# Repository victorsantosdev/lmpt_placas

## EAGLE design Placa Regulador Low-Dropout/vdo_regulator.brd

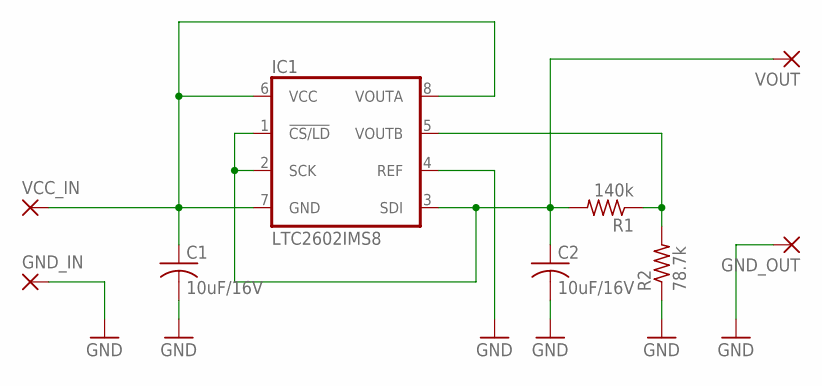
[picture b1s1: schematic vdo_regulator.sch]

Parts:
C1, C2: 10uF/16V; C025-025X050
GND_IN: 2,54/0,9
GND_OUT: 2,54/0,9
IC1: LTC2602IMS8; MSOP8
R1: 140k; 0309/10
R2: 78.7k; 0309/10
VCC_IN: 2,54/0,9
VOUT: 2,54/0,9

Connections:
GND: C1.2, C2.2, GND_IN.1, GND_OUT.1, IC1.4 (REF), R2.1
unnamed: C1.1, IC1.6 (VCC), IC1.7 (GND), IC1.8 (VOUTA), VCC_IN.1
unnamed: C2.1, IC1.1 (!CS/LD), IC1.2 (SCK), IC1.3 (SDI), R1.2, VOUT.1
unnamed: IC1.5 (VOUTB), R1.1, R2.2

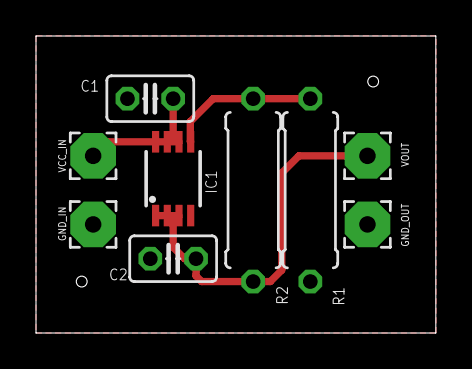
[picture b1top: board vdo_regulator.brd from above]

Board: 2 copper layers, 22.2 x 16.5 mm, 9 parts (0 on the bottom side), 4 nets.

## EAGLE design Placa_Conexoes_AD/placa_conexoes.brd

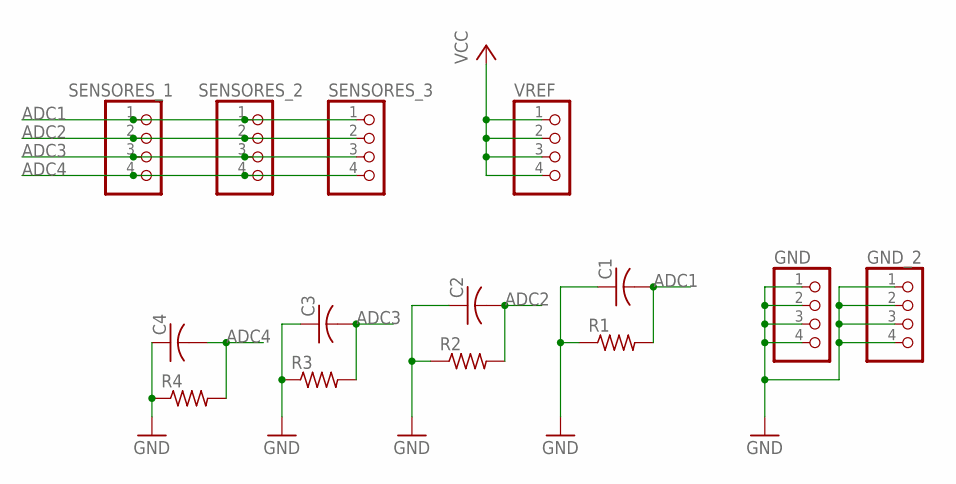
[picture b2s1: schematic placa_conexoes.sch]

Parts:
C1, C2, C3, C4: C-US025-025X050; C025-025X050
GND: PINHD-1X4; 1X04
GND_2: PINHD-1X4; 1X04
R1, R2, R3, R4: R-US_0207/9; 0207/9
SENSORES_1, SENSORES_2, SENSORES_3: PINHD-1X4; 1X04
VREF: PINHD-1X4; 1X04

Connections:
ADC1: C1.2, R1.2, SENSORES_1.1, SENSORES_2.1, SENSORES_3.1
ADC2: C2.2, R2.2, SENSORES_1.2, SENSORES_2.2, SENSORES_3.2
ADC3: C3.2, R3.2, SENSORES_1.3, SENSORES_2.3, SENSORES_3.3
ADC4: C4.2, R4.2, SENSORES_1.4, SENSORES_2.4, SENSORES_3.4
GND: C1.1, C2.1, C3.1, C4.1, GND.1, GND.2, GND.3, GND.4, GND_2.1, GND_2.2, GND_2.3, GND_2.4, R1.1, R2.1, R3.1, R4.1
VCC: VREF.1, VREF.2, VREF.3, VREF.4

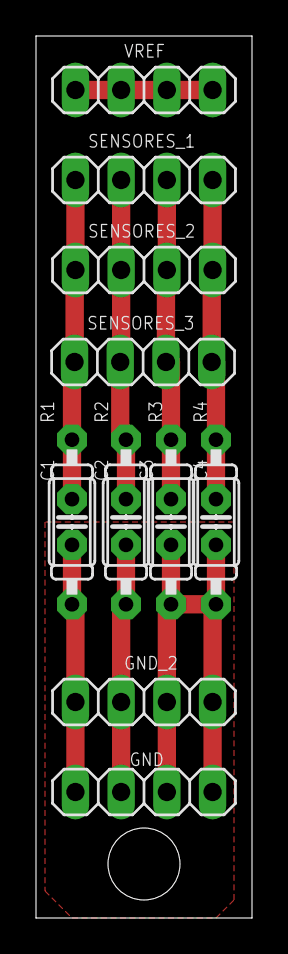
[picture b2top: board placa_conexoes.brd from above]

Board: 2 copper layers, 12.0 x 49.0 mm, 14 parts (0 on the bottom side), 6 nets.

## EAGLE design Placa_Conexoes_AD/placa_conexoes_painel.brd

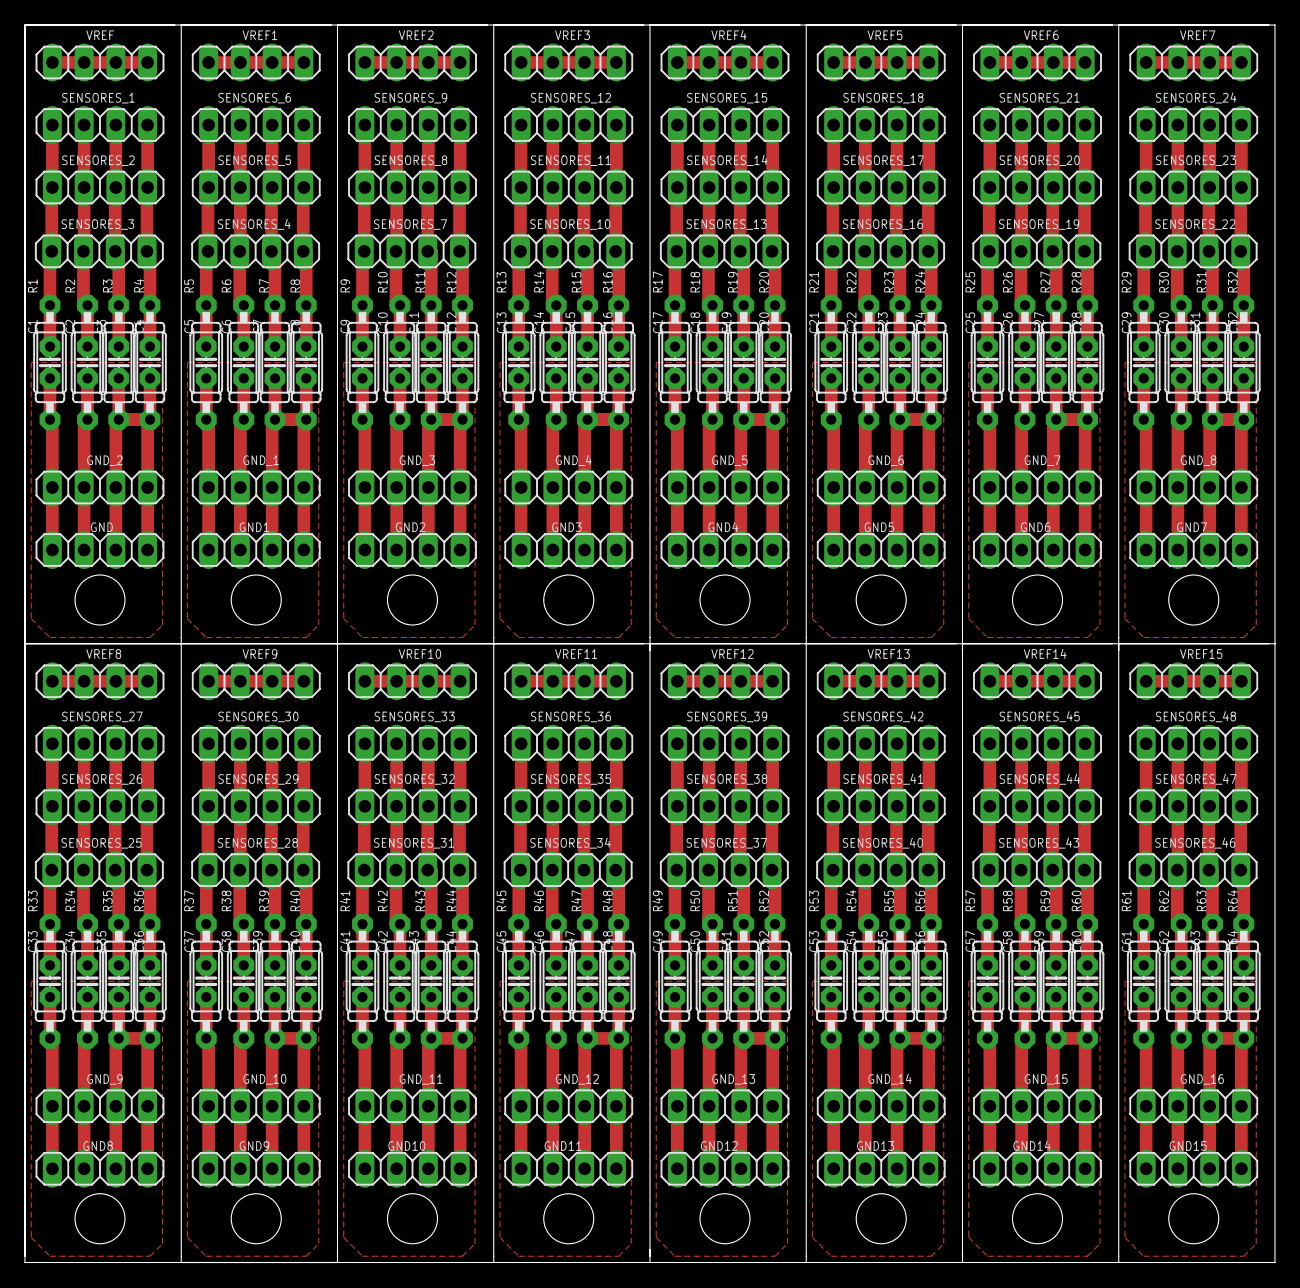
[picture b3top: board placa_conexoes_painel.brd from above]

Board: 2 copper layers, 100.0 x 99.0 mm, 224 parts (0 on the bottom side), 96 nets.

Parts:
C1, C2, C3, C4, C5, C6, C7, C8, C9, C10, C11, C12, C13, C14, C15, C16, C17, C18, C19, C20, C21, C22, C23, C24, C25, C26, C27, C28, C29, C30, C31, C32, C33, C34, C35, C36, C37, C38, C39, C40, C41, C42, C43, C44, C45, C46, C47, C48, C49, C50, C51, C52, C53, C54, C55, C56, C57, C58, C59, C60, C61, C62, C63, C64: C025-025X050
GND, GND1, GND2, GND3, GND4, GND5, GND6, GND7, GND8, GND9, GND10, GND11, GND12, GND13, GND14, GND15: 1X04
GND_1, GND_2, GND_3, GND_4, GND_5, GND_6, GND_7, GND_8, GND_9, GND_10, GND_11, GND_12, GND_13, GND_14, GND_15, GND_16: 1X04
R1, R2, R3, R4, R5, R6, R7, R8, R9, R10, R11, R12, R13, R14, R15, R16, R17, R18, R19, R20, R21, R22, R23, R24, R25, R26, R27, R28, R29, R30, R31, R32, R33, R34, R35, R36, R37, R38, R39, R40, R41, R42, R43, R44, R45, R46, R47, R48, R49, R50, R51, R52, R53, R54, R55, R56, R57, R58, R59, R60, R61, R62, R63, R64: 0207/9
SENSORES_1, SENSORES_2, SENSORES_3, SENSORES_4, SENSORES_5, SENSORES_6, SENSORES_7, SENSORES_8, SENSORES_9, SENSORES_10, SENSORES_11, SENSORES_12, SENSORES_13, SENSORES_14, SENSORES_15, SENSORES_16, SENSORES_17, SENSORES_18, SENSORES_19, SENSORES_20, SENSORES_21, SENSORES_22, SENSORES_23, SENSORES_24, SENSORES_25, SENSORES_26, SENSORES_27, SENSORES_28, SENSORES_29, SENSORES_30, SENSORES_31, SENSORES_32, SENSORES_33, SENSORES_34, SENSORES_35, SENSORES_36, SENSORES_37, SENSORES_38, SENSORES_39, SENSORES_40, SENSORES_41, SENSORES_42, SENSORES_43, SENSORES_44, SENSORES_45, SENSORES_46, SENSORES_47, SENSORES_48: 1X04
VREF, VREF1, VREF2, VREF3, VREF4, VREF5, VREF6, VREF7, VREF8, VREF9, VREF10, VREF11, VREF12, VREF13, VREF14, VREF15: 1X04

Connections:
ADC1: C1.2, R1.2, SENSORES_1.1, SENSORES_2.1, SENSORES_3.1
ADC2: C2.2, R2.2, SENSORES_1.2, SENSORES_2.2, SENSORES_3.2
ADC3: C3.2, R3.2, SENSORES_1.3, SENSORES_2.3, SENSORES_3.3
ADC4: C4.2, R4.2, SENSORES_1.4, SENSORES_2.4, SENSORES_3.4
ADC5: C8.2, R8.2, SENSORES_4.4, SENSORES_5.4, SENSORES_6.4
ADC6: C7.2, R7.2, SENSORES_4.3, SENSORES_5.3, SENSORES_6.3
ADC7: C6.2, R6.2, SENSORES_4.2, SENSORES_5.2, SENSORES_6.2
ADC8: C5.2, R5.2, SENSORES_4.1, SENSORES_5.1, SENSORES_6.1
ADC9: C12.2, R12.2, SENSORES_7.4, SENSORES_8.4, SENSORES_9.4
ADC10: C11.2, R11.2, SENSORES_7.3, SENSORES_8.3, SENSORES_9.3
ADC11: C10.2, R10.2, SENSORES_7.2, SENSORES_8.2, SENSORES_9.2
ADC12: C9.2, R9.2, SENSORES_7.1, SENSORES_8.1, SENSORES_9.1
ADC13: C16.2, R16.2, SENSORES_10.4, SENSORES_11.4, SENSORES_12.4
ADC14: C15.2, R15.2, SENSORES_10.3, SENSORES_11.3, SENSORES_12.3
ADC15: C14.2, R14.2, SENSORES_10.2, SENSORES_11.2, SENSORES_12.2
ADC16: C13.2, R13.2, SENSORES_10.1, SENSORES_11.1, SENSORES_12.1
ADC17: C20.2, R20.2, SENSORES_13.4, SENSORES_14.4, SENSORES_15.4
ADC18: C19.2, R19.2, SENSORES_13.3, SENSORES_14.3, SENSORES_15.3
ADC19: C18.2, R18.2, SENSORES_13.2, SENSORES_14.2, SENSORES_15.2
ADC20: C17.2, R17.2, SENSORES_13.1, SENSORES_14.1, SENSORES_15.1
ADC21: C24.2, R24.2, SENSORES_16.4, SENSORES_17.4, SENSORES_18.4
ADC22: C23.2, R23.2, SENSORES_16.3, SENSORES_17.3, SENSORES_18.3
ADC23: C22.2, R22.2, SENSORES_16.2, SENSORES_17.2, SENSORES_18.2
ADC24: C21.2, R21.2, SENSORES_16.1, SENSORES_17.1, SENSORES_18.1
ADC25: C28.2, R28.2, SENSORES_19.4, SENSORES_20.4, SENSORES_21.4
ADC26: C27.2, R27.2, SENSORES_19.3, SENSORES_20.3, SENSORES_21.3
ADC27: C26.2, R26.2, SENSORES_19.2, SENSORES_20.2, SENSORES_21.2
ADC28: C25.2, R25.2, SENSORES_19.1, SENSORES_20.1, SENSORES_21.1
ADC29: C32.2, R32.2, SENSORES_22.4, SENSORES_23.4, SENSORES_24.4
ADC30: C31.2, R31.2, SENSORES_22.3, SENSORES_23.3, SENSORES_24.3
ADC31: C30.2, R30.2, SENSORES_22.2, SENSORES_23.2, SENSORES_24.2
ADC32: C29.2, R29.2, SENSORES_22.1, SENSORES_23.1, SENSORES_24.1
ADC33: C36.2, R36.2, SENSORES_25.4, SENSORES_26.4, SENSORES_27.4
ADC34: C35.2, R35.2, SENSORES_25.3, SENSORES_26.3, SENSORES_27.3
ADC35: C34.2, R34.2, SENSORES_25.2, SENSORES_26.2, SENSORES_27.2
ADC36: C33.2, R33.2, SENSORES_25.1, SENSORES_26.1, SENSORES_27.1
ADC37: C40.2, R40.2, SENSORES_28.4, SENSORES_29.4, SENSORES_30.4
ADC38: C39.2, R39.2, SENSORES_28.3, SENSORES_29.3, SENSORES_30.3
ADC39: C38.2, R38.2, SENSORES_28.2, SENSORES_29.2, SENSORES_30.2
ADC40: C37.2, R37.2, SENSORES_28.1, SENSORES_29.1, SENSORES_30.1
ADC41: C44.2, R44.2, SENSORES_31.4, SENSORES_32.4, SENSORES_33.4
ADC42: C43.2, R43.2, SENSORES_31.3, SENSORES_32.3, SENSORES_33.3
ADC43: C42.2, R42.2, SENSORES_31.2, SENSORES_32.2, SENSORES_33.2
ADC44: C41.2, R41.2, SENSORES_31.1, SENSORES_32.1, SENSORES_33.1
ADC45: C48.2, R48.2, SENSORES_34.4, SENSORES_35.4, SENSORES_36.4
ADC46: C47.2, R47.2, SENSORES_34.3, SENSORES_35.3, SENSORES_36.3
ADC47: C46.2, R46.2, SENSORES_34.2, SENSORES_35.2, SENSORES_36.2
ADC48: C45.2, R45.2, SENSORES_34.1, SENSORES_35.1, SENSORES_36.1
ADC49: C52.2, R52.2, SENSORES_37.4, SENSORES_38.4, SENSORES_39.4
ADC50: C51.2, R51.2, SENSORES_37.3, SENSORES_38.3, SENSORES_39.3
ADC51: C50.2, R50.2, SENSORES_37.2, SENSORES_38.2, SENSORES_39.2
ADC52: C49.2, R49.2, SENSORES_37.1, SENSORES_38.1, SENSORES_39.1
ADC53: C56.2, R56.2, SENSORES_40.4, SENSORES_41.4, SENSORES_42.4
ADC54: C55.2, R55.2, SENSORES_40.3, SENSORES_41.3, SENSORES_42.3
ADC55: C54.2, R54.2, SENSORES_40.2, SENSORES_41.2, SENSORES_42.2
ADC56: C53.2, R53.2, SENSORES_40.1, SENSORES_41.1, SENSORES_42.1
ADC57: C60.2, R60.2, SENSORES_43.4, SENSORES_44.4, SENSORES_45.4
ADC58: C59.2, R59.2, SENSORES_43.3, SENSORES_44.3, SENSORES_45.3
ADC59: C58.2, R58.2, SENSORES_43.2, SENSORES_44.2, SENSORES_45.2
ADC60: C57.2, R57.2, SENSORES_43.1, SENSORES_44.1, SENSORES_45.1
ADC61: C64.2, R64.2, SENSORES_46.4, SENSORES_47.4, SENSORES_48.4
ADC62: C63.2, R63.2, SENSORES_46.3, SENSORES_47.3, SENSORES_48.3
ADC63: C62.2, R62.2, SENSORES_46.2, SENSORES_47.2, SENSORES_48.2
ADC64: C61.2, R61.2, SENSORES_46.1, SENSORES_47.1, SENSORES_48.1
GND: C1.1, C2.1, C3.1, C4.1, GND.1, GND.2, GND.3, GND.4, GND_2.1, GND_2.2, GND_2.3, GND_2.4, R1.1, R2.1, R3.1, R4.1
GND1: C5.1, C6.1, C7.1, C8.1, GND1.1, GND1.2, GND1.3, GND1.4, GND_1.1, GND_1.2, GND_1.3, GND_1.4, R5.1, R6.1, R7.1, R8.1
GND2: C9.1, C10.1, C11.1, C12.1, GND2.1, GND2.2, GND2.3, GND2.4, GND_3.1, GND_3.2, GND_3.3, GND_3.4, R9.1, R10.1, R11.1, R12.1
GND3: C13.1, C14.1, C15.1, C16.1, GND3.1, GND3.2, GND3.3, GND3.4, GND_4.1, GND_4.2, GND_4.3, GND_4.4, R13.1, R14.1, R15.1, R16.1
GND4: C17.1, C18.1, C19.1, C20.1, GND4.1, GND4.2, GND4.3, GND4.4, GND_5.1, GND_5.2, GND_5.3, GND_5.4, R17.1, R18.1, R19.1, R20.1
GND5: C21.1, C22.1, C23.1, C24.1, GND5.1, GND5.2, GND5.3, GND5.4, GND_6.1, GND_6.2, GND_6.3, GND_6.4, R21.1, R22.1, R23.1, R24.1
GND6: C25.1, C26.1, C27.1, C28.1, GND6.1, GND6.2, GND6.3, GND6.4, GND_7.1, GND_7.2, GND_7.3, GND_7.4, R25.1, R26.1, R27.1, R28.1
GND7: C29.1, C30.1, C31.1, C32.1, GND7.1, GND7.2, GND7.3, GND7.4, GND_8.1, GND_8.2, GND_8.3, GND_8.4, R29.1, R30.1, R31.1, R32.1
GND8: C33.1, C34.1, C35.1, C36.1, GND8.1, GND8.2, GND8.3, GND8.4, GND_9.1, GND_9.2, GND_9.3, GND_9.4, R33.1, R34.1, R35.1, R36.1
GND9: C37.1, C38.1, C39.1, C40.1, GND9.1, GND9.2, GND9.3, GND9.4, GND_10.1, GND_10.2, GND_10.3, GND_10.4, R37.1, R38.1, R39.1, R40.1
GND10: C41.1, C42.1, C43.1, C44.1, GND10.1, GND10.2, GND10.3, GND10.4, GND_11.1, GND_11.2, GND_11.3, GND_11.4, R41.1, R42.1, R43.1, R44.1
GND11: C45.1, C46.1, C47.1, C48.1, GND11.1, GND11.2, GND11.3, GND11.4, GND_12.1, GND_12.2, GND_12.3, GND_12.4, R45.1, R46.1, R47.1, R48.1
GND12: C49.1, C50.1, C51.1, C52.1, GND12.1, GND12.2, GND12.3, GND12.4, GND_13.1, GND_13.2, GND_13.3, GND_13.4, R49.1, R50.1, R51.1, R52.1
GND13: C53.1, C54.1, C55.1, C56.1, GND13.1, GND13.2, GND13.3, GND13.4, GND_14.1, GND_14.2, GND_14.3, GND_14.4, R53.1, R54.1, R55.1, R56.1
GND14: C57.1, C58.1, C59.1, C60.1, GND14.1, GND14.2, GND14.3, GND14.4, GND_15.1, GND_15.2, GND_15.3, GND_15.4, R57.1, R58.1, R59.1, R60.1
GND15: C61.1, C62.1, C63.1, C64.1, GND15.1, GND15.2, GND15.3, GND15.4, GND_16.1, GND_16.2, GND_16.3, GND_16.4, R61.1, R62.1, R63.1, R64.1
VCC: VREF.1, VREF.2, VREF.3, VREF.4
VCC1: VREF1.1, VREF1.2, VREF1.3, VREF1.4
VCC2: VREF2.1, VREF2.2, VREF2.3, VREF2.4
VCC3: VREF3.1, VREF3.2, VREF3.3, VREF3.4
VCC4: VREF4.1, VREF4.2, VREF4.3, VREF4.4
VCC5: VREF5.1, VREF5.2, VREF5.3, VREF5.4
VCC6: VREF6.1, VREF6.2, VREF6.3, VREF6.4
VCC7: VREF7.1, VREF7.2, VREF7.3, VREF7.4
VCC8: VREF8.1, VREF8.2, VREF8.3, VREF8.4
VCC9: VREF9.1, VREF9.2, VREF9.3, VREF9.4
VCC10: VREF10.1, VREF10.2, VREF10.3, VREF10.4
VCC11: VREF11.1, VREF11.2, VREF11.3, VREF11.4
VCC12: VREF12.1, VREF12.2, VREF12.3, VREF12.4
VCC13: VREF13.1, VREF13.2, VREF13.3, VREF13.4
VCC14: VREF14.1, VREF14.2, VREF14.3, VREF14.4
VCC15: VREF15.1, VREF15.2, VREF15.3, VREF15.4

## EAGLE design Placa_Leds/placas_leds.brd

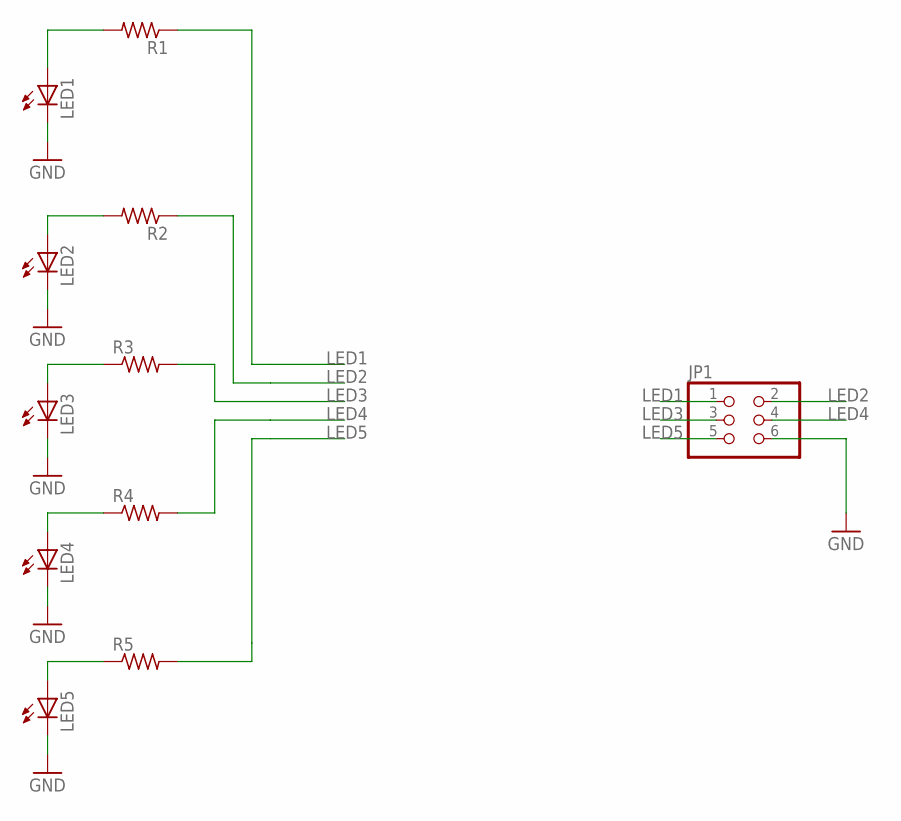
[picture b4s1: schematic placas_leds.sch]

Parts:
JP1: PINHD-2X3; 2X03
LED1, LED2, LED3, LED4, LED5: LED5MM
R1, R2, R3, R4, R5: R-US_0207/9; 0207/9

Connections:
GND: JP1.6, LED1.K (C), LED2.K (C), LED3.K (C), LED4.K (C), LED5.K (C)
LED1: JP1.1, R1.1
LED2: JP1.2, R2.1
LED3: JP1.3, R3.2
LED4: JP1.4, R4.2
LED5: JP1.5, R5.2
unnamed: LED2.A, R2.2
unnamed: LED1.A, R1.2
unnamed: LED3.A, R3.1
unnamed: LED4.A, R4.1
unnamed: LED5.A, R5.1

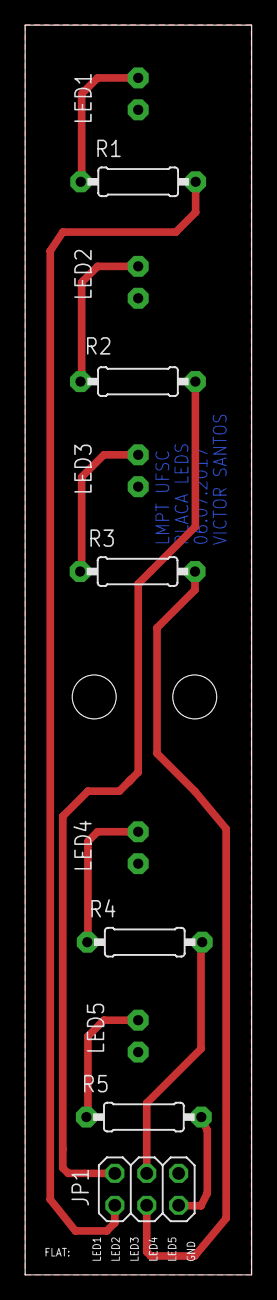
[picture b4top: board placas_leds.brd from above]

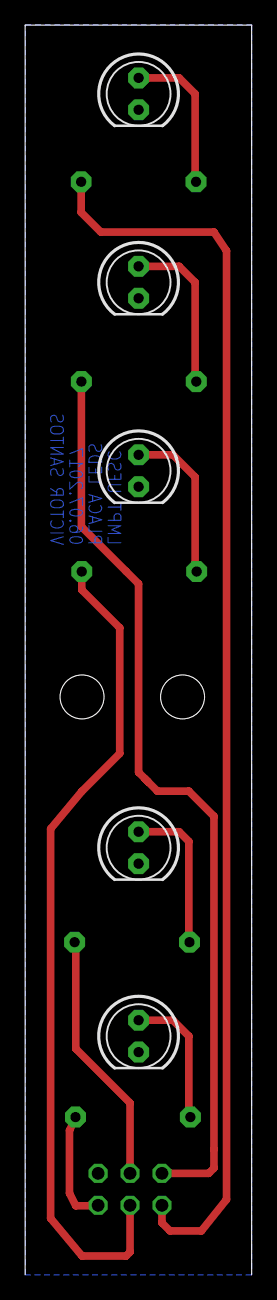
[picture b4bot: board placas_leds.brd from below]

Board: 2 copper layers, 18.0 x 99.5 mm, 11 parts (5 on the bottom side), 11 nets.

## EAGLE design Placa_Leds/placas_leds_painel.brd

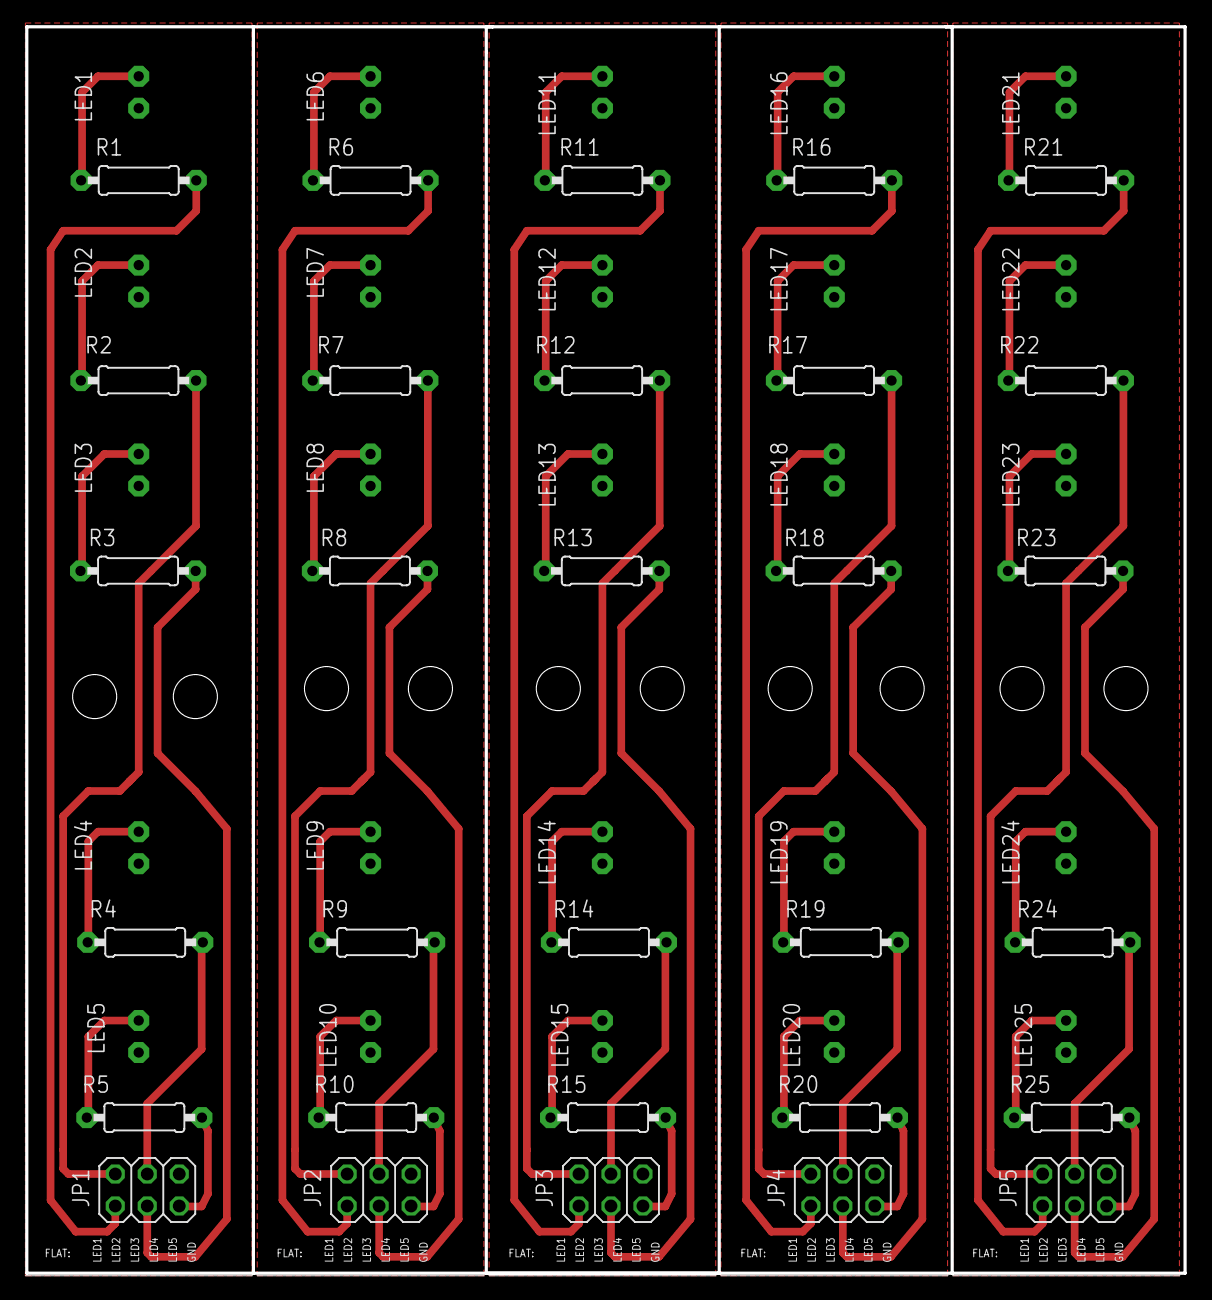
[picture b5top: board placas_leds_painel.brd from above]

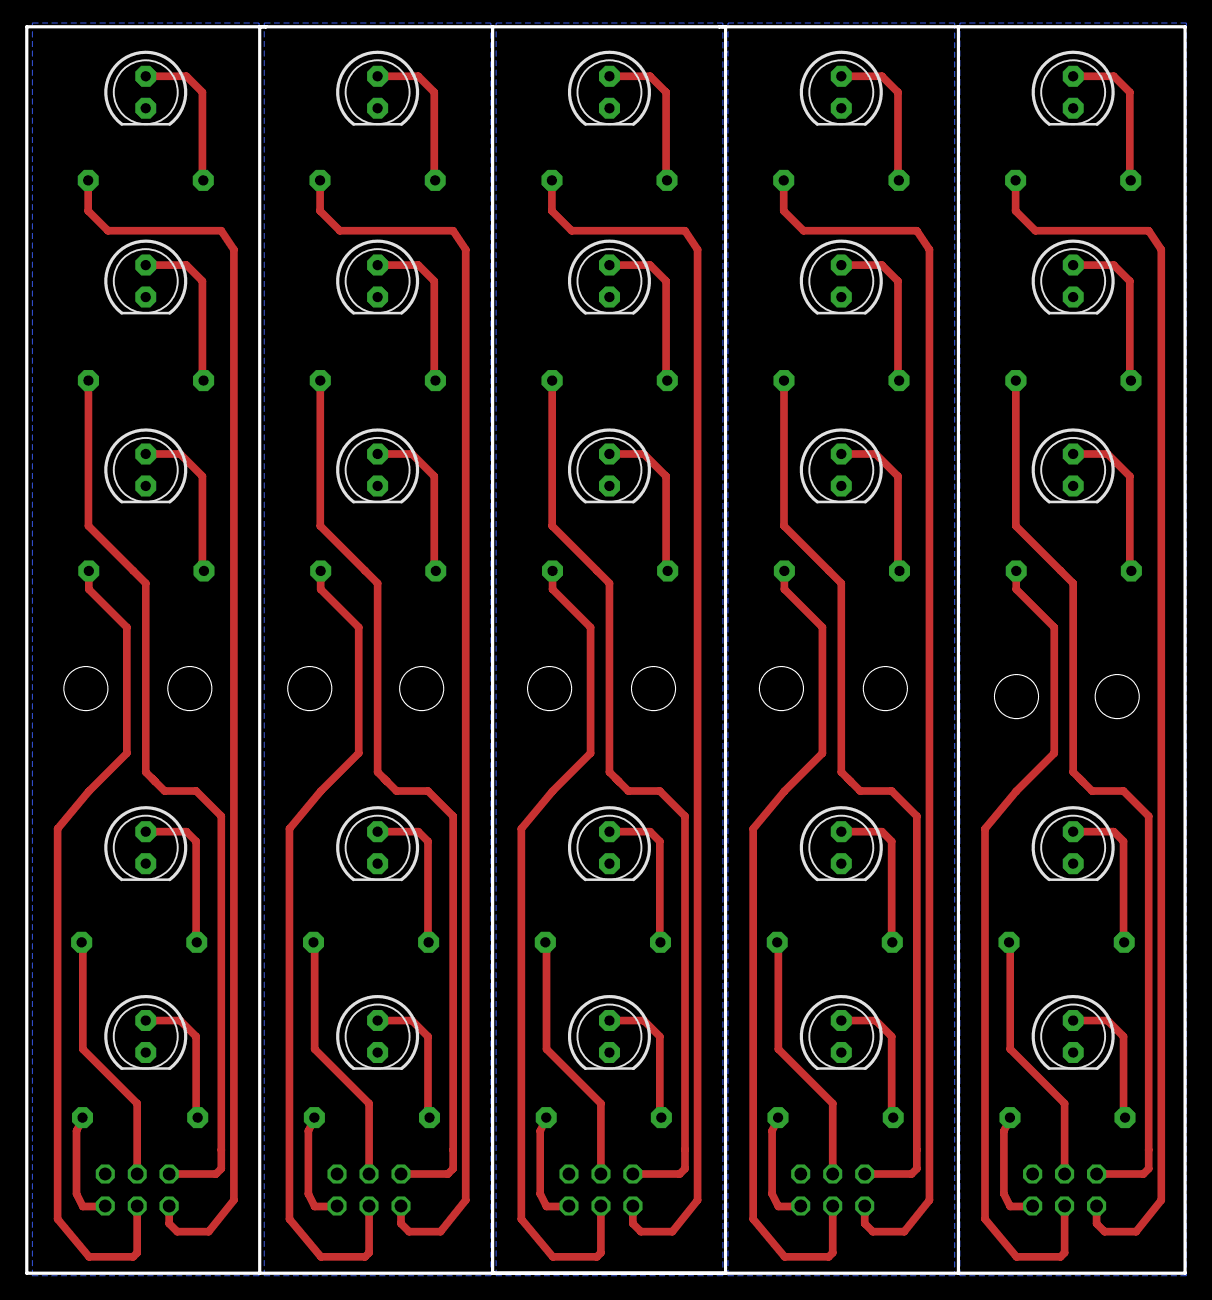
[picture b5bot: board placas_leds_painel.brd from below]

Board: 2 copper layers, 92.0 x 99.0 mm, 55 parts (25 on the bottom side), 55 nets.

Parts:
JP1, JP2, JP3, JP4, JP5: 2X03
LED1, LED2, LED3, LED4, LED5, LED6, LED7, LED8, LED9, LED10, LED11, LED12, LED13, LED14, LED15, LED16, LED17, LED18, LED19, LED20, LED21, LED22, LED23, LED24, LED25: LED5MM
R1, R2, R3, R4, R5, R6, R7, R8, R9, R10, R11, R12, R13, R14, R15, R16, R17, R18, R19, R20, R21, R22, R23, R24, R25: 0207/9

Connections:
GND: JP1.6, LED1.K, LED2.K, LED3.K, LED4.K, LED5.K
GND1: JP2.6, LED6.K, LED7.K, LED8.K, LED9.K, LED10.K
GND2: JP3.6, LED11.K, LED12.K, LED13.K, LED14.K, LED15.K
GND3: JP4.6, LED16.K, LED17.K, LED18.K, LED19.K, LED20.K
GND4: JP5.6, LED21.K, LED22.K, LED23.K, LED24.K, LED25.K
LED1: JP1.1, R1.1
LED2: JP1.2, R2.1
LED3: JP1.3, R3.2
LED4: JP1.4, R4.2
LED5: JP1.5, R5.2
LED6: JP2.1, R6.1
LED7: JP2.2, R7.1
LED8: JP2.3, R8.2
LED9: JP2.4, R9.2
LED10: JP2.5, R10.2
LED11: JP3.1, R11.1
LED12: JP3.2, R12.1
LED13: JP3.3, R13.2
LED14: JP3.4, R14.2
LED15: JP3.5, R15.2
LED16: JP4.1, R16.1
LED17: JP4.2, R17.1
LED18: JP4.3, R18.2
LED19: JP4.4, R19.2
LED20: JP4.5, R20.2
LED21: JP5.1, R21.1
LED22: JP5.2, R22.1
LED23: JP5.3, R23.2
LED24: JP5.4, R24.2
LED25: JP5.5, R25.2
unnamed: LED2.A, R2.2
unnamed: LED6.A, R6.2
unnamed: LED7.A, R7.2
unnamed: LED8.A, R8.1
unnamed: LED9.A, R9.1
unnamed: LED10.A, R10.1
unnamed: LED1.A, R1.2
unnamed: LED3.A, R3.1
unnamed: LED4.A, R4.1
unnamed: LED5.A, R5.1
unnamed: LED11.A, R11.2
unnamed: LED12.A, R12.2
unnamed: LED13.A, R13.1
unnamed: LED14.A, R14.1
unnamed: LED15.A, R15.1
unnamed: LED16.A, R16.2
unnamed: LED17.A, R17.2
unnamed: LED18.A, R18.1
unnamed: LED19.A, R19.1
unnamed: LED20.A, R20.1
unnamed: LED21.A, R21.2
unnamed: LED22.A, R22.2
unnamed: LED23.A, R23.1
unnamed: LED24.A, R24.1
unnamed: LED25.A, R25.1
